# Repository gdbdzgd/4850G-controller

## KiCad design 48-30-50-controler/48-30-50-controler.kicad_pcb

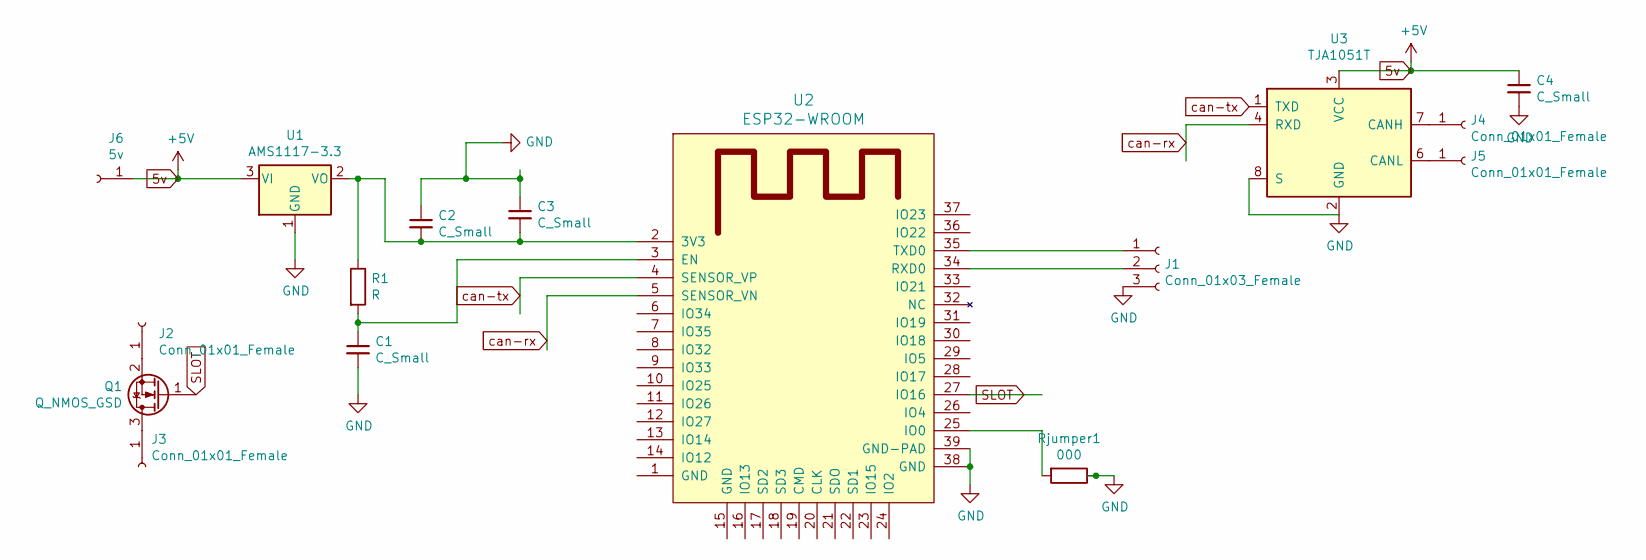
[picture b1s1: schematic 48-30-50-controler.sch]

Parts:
C1, C2, C3, C4: C_Small; C_0402_1005Metric
J1: Conn_01x03_Female; PinHeader_1x03_P1.00mm_Vertical
J2, J3, J4, J5: Conn_01x01_Female; PinHeader_1x01_P1.00mm_Vertical
J6: 5v; PinHeader_1x01_P1.00mm_Vertical
Q1: Q_NMOS_GSD; TSOT-23
R1: R; R_0402_1005Metric
Rjumper1: 000; R_0402_1005Metric
U1: AMS1117-3.3; SOT-223-3_TabPin2
U2: ESP32-WROOM
U3: TJA1051T; SOIC-8_3.9x4.9mm_P1.27mm

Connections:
5v: C4.1, J6.1, U1.3 (VI), U3.3 (VCC)
GND: C1.2, C2.1, C3.1, C4.2, J1.3, Rjumper1.1, U1.1 (GND), U2.38 (GND), U2.39 (GND-PAD), U3.2 (GND), U3.8 (S)
unnamed: C1.1, R1.2, U2.3 (EN)
unnamed: C2.2, C3.2, R1.1, U1.2 (VO), U2.2 (3V3)
unnamed: J1.1, U2.35 (TXD0)
unnamed: J1.2, U2.34 (RXD0)
unnamed: J2.1, Q1.2 (S)
unnamed: J3.1, Q1.3 (D)
unnamed: J4.1, U3.7 (CANH)
unnamed: J5.1, U3.6 (CANL)
unnamed: Rjumper1.2, U2.25 (IO0)
SLOT: Q1.1 (G), U2.27 (IO16)
can-rx: U2.5 (SENSOR_VN), U3.4 (RXD)
can-tx: U2.4 (SENSOR_VP), U3.1 (TXD)

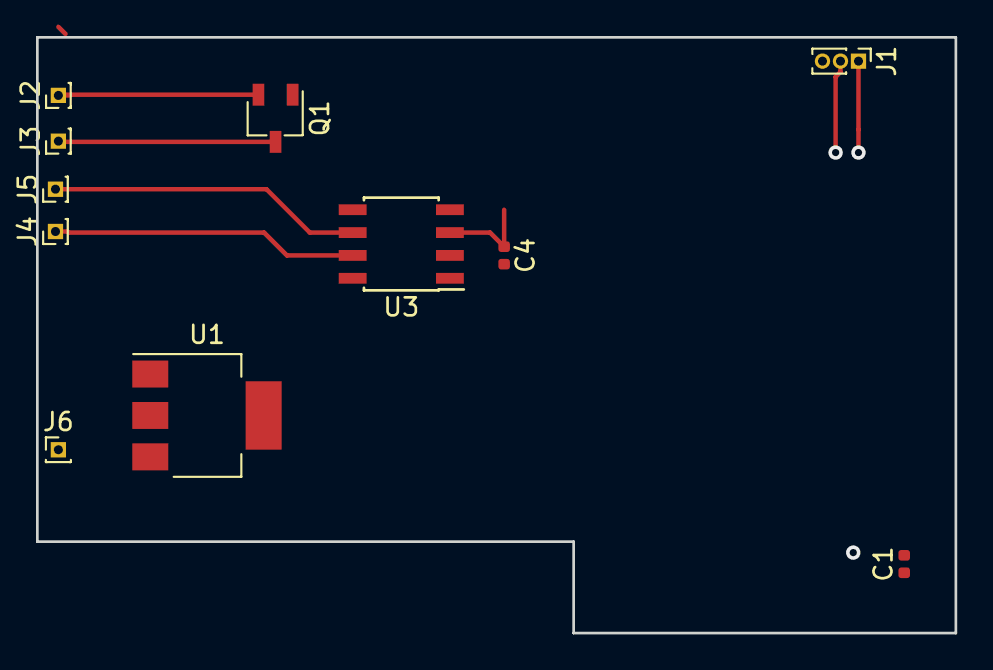
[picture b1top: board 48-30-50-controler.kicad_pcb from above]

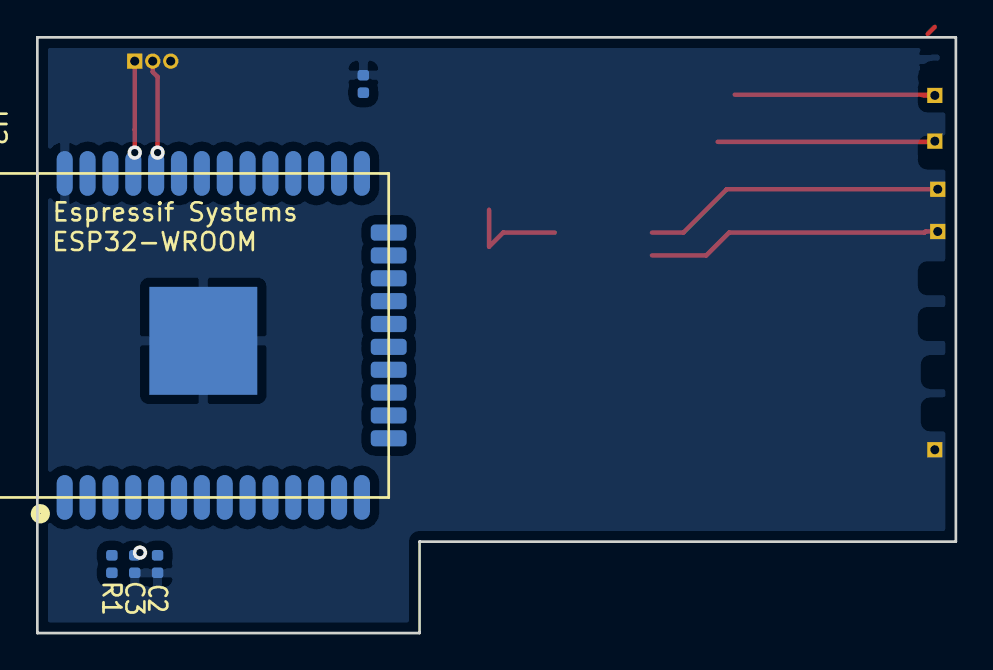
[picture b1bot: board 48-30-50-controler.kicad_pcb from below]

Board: 2 copper layers, 51.0 x 33.1 mm, 16 parts (5 on the bottom side), 14 nets.

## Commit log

2018-11-15 init
2019-08-23 新文件： swlder/ESP32_TFT_eSPI/ESP32_TFT_eSPI.ino
    新文件： swlder/TFT_eSPI/Extensions/Button.cpp
